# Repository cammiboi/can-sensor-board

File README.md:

# can-sensor-board

# Pupose
To attach any I2C sensor to a CAN bus.

# Requirements
* Powered by 5-16V DC
* Input and output connector (daisy chain boards)
* Set address on board
* I2C 4 pin connector to quickly connect different sensor boards
* Programming header
* ESD protection on connector pins

# Pinout
### CAN and Power Connectors (J1 and J2)

Both of these connectors are the same, you can plug input OR output in to either one.

Wire connector: Molex 1053081204

| Pin Number | Function |
|--|--|
|1| CAN H |
|2 | CAN L |
|3 | VIN |
|4 | GND|

### I2C Connectors (J3 and J4)

Works with Sensor boards that have Adafruit STEMMA QT or Sparkfun QWIIC connector.

| Pin Number | Function |
|--|--|
|1| GND |
|2 | 3V3 |
|3 | SDA |
|4 | SCL|

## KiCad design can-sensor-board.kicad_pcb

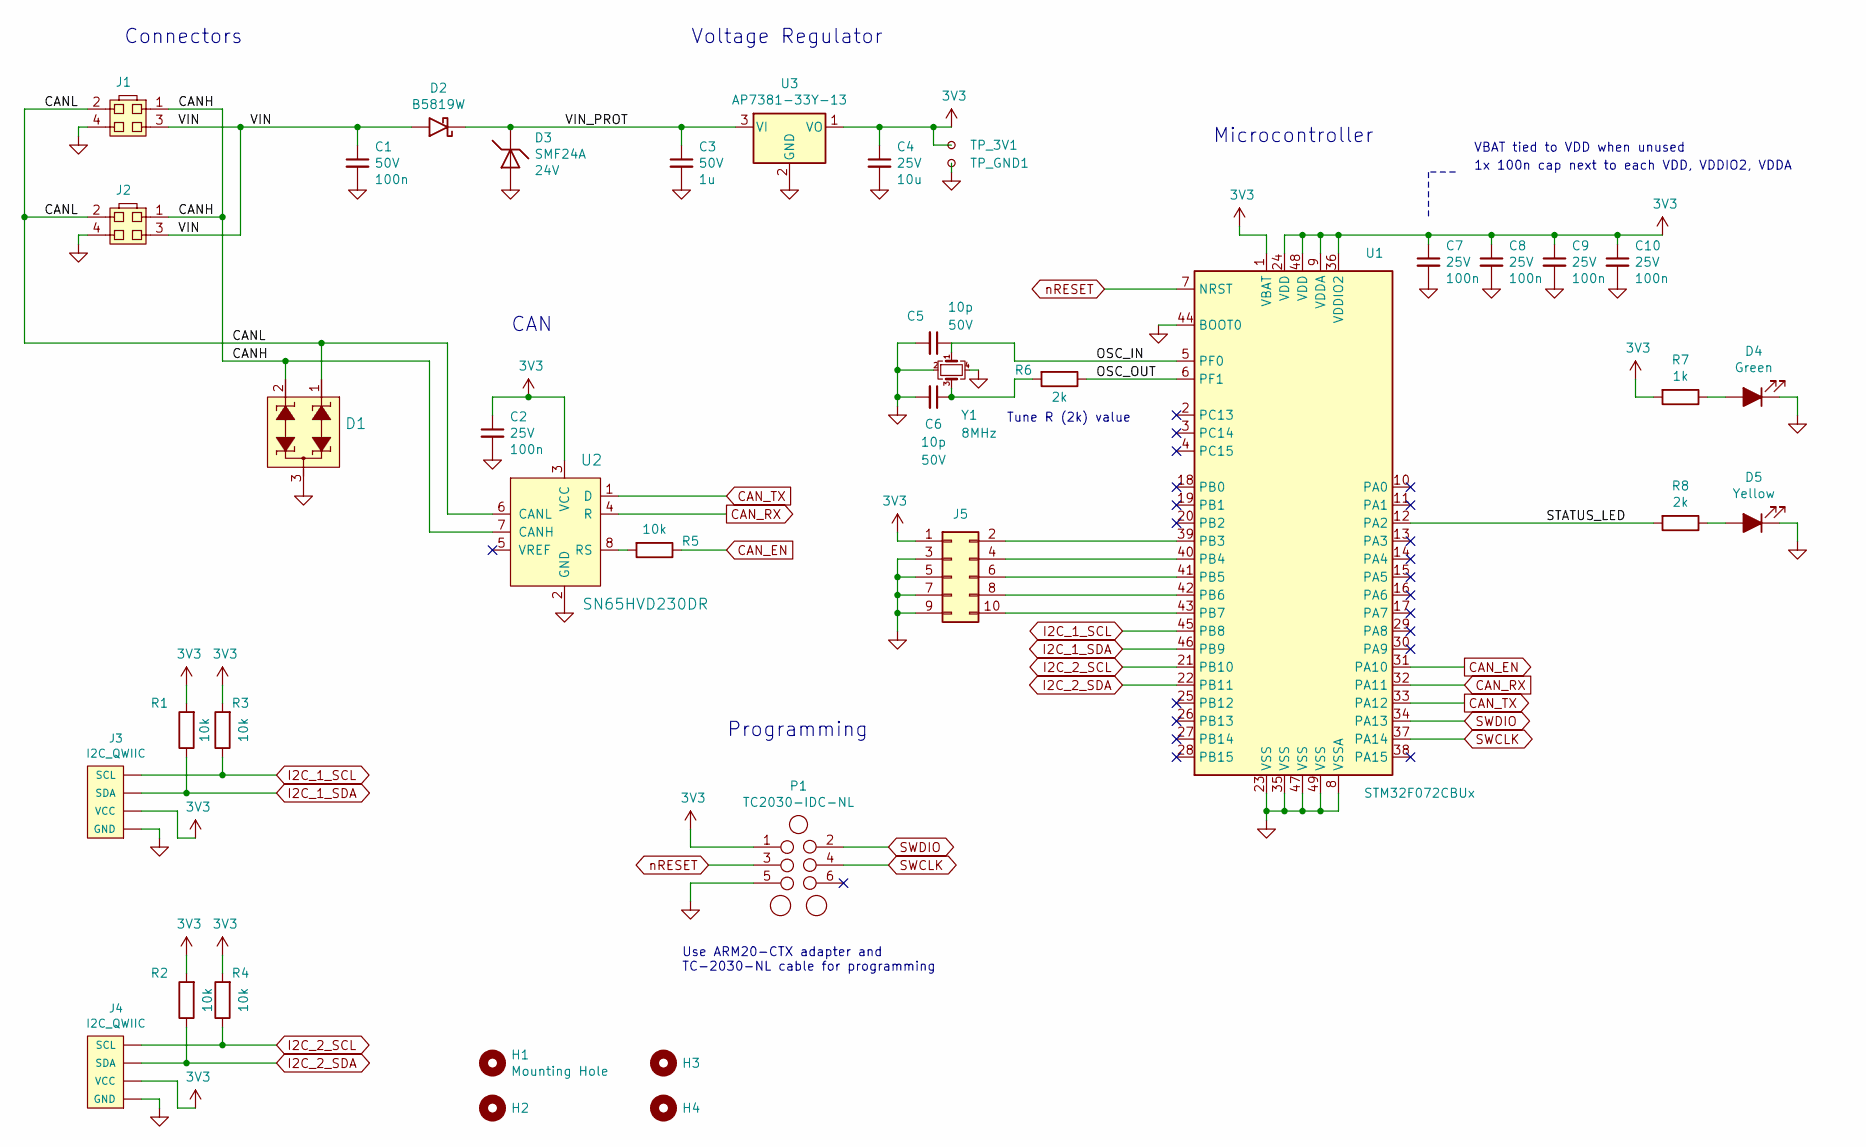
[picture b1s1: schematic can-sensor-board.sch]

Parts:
C1: C_0603_50V_X7R_100n; C_0603_1608Metric; Voltage 50V; Part Number CL10B104KB8NFNC; JLC C14663
C2, C7, C8, C9, C10: C_0402_25V_X7R_100n; C_0402_1005Metric; Voltage 25V; Manufacturer Part Number CL05B104KA5NNNC; JLC C100072
C3: C_0805_50V_X7R_1u; C_0805_2012Metric; Voltage 50V; Part Number CL21B105KBFNNNG; JLC C28323
C4: C_0805_25V_X5R_10u; C_0805_2012Metric; Voltage 25V; Part Number CL21A106KAYNNNG; JLC C15850
C5, C6: C_0402_50V_COG_10p; C_0402_1005Metric; Voltage 50V; JLC C32949
D1: PESD2CAN_215; SOT-23; MPN PESD2CAN,215; Digi-Key_PN 1727-3891-1-ND
D2: B5819W; D_SOD-123; Voltage 40V; JLC C8598
D3: SMF24A; D_SOD-123F; JLC C169430
D4: LED_0603_Green; LED_0603_1608Metric; JLC C72043
D5: LED_0603_Yellow; LED_0603_1608Metric; JLC C72038
H1, H2, H3, H4: Mounting Hole; MountingHole_3.2mm_M3; JLCPCB_IGNORE Yes
J1, J2: 105314-1104; Molex_Nano-Fit_105314-xx04_2x02_P2.50mm_Horizontal; JLCPCB_IGNORE Yes
J3, J4: I2C_QWIIC; JST_SH_SM04B-SRSS-TB_1x04-1MP_P1.00mm_Horizontal; Part Number SM04B-SRSS-TB(LF)(SN); JLC C395301
J5: Conn_02x05_Odd_Even; PinHeader_2x05_P2.54mm_Vertical; JLCPCB_IGNORE Yes
P1: TC2030-IDC-NL; Tag-Connect_TC2030-IDC-NL_2x03_P1.27mm_Vertical; JLCPCB_IGNORE Yes
R1, R2, R3, R4, R5: R_0603_10k_1; R_0603_1608Metric; JLC C25804
R6, R8: R_0402_2k_1; R_0402_1005Metric; JLC C4109
R7: R_0402_1k_1; R_0402_1005Metric; JLC C11702
TP_3V1: TestPoint_Small; TestPoint_Pad_D1.00mm; JLCPCB_IGNORE Yes
TP_GND1: TestPoint_Small; TestPoint_Pad_D1.00mm; JLCPCB_IGNORE Yes
U1: STM32F072CBUx; QFN-48-1EP_7x7mm_P0.5mm_EP5.6x5.6mm; JLC C92504
U2: SN65HVD230DR; SOIC-8_3.9x4.9mm_P1.27mm; MPN SN65HVD230DR; Digi-Key_PN 296-11654-1-ND
U3: AP7381-33Y-13; SOT-89-3; JLC C460411
Y1: TAXM8M4RDBCCT2T; Crystal_SMD_3225-4Pin_3.2x2.5mm; JLC C400090

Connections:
3V3: C2.1, C4.1, C7.1, C8.1, C9.1, C10.1, J3.2 (VCC), J4.2 (VCC), J5.1, P1.1, R1.2, R2.2, R3.2, R4.2, R7.2, TP_3V1.1, U1.1 (VBAT), U1.9 (VDDA), U1.24 (VDD), U1.36 (VDDIO2), U1.48 (VDD), U2.3 (VCC), U3.1 (VO)
/CANH: D1.2 (C2), J1.1, J2.1, U2.7 (CANH)
/CANL: D1.1 (C1), J1.2, J2.2, U2.6 (CANL)
/OSC_IN: C5.1, U1.5 (PF0), Y1.1
/OSC_OUT: R6.1, U1.6 (PF1)
/STATUS_LED: R8.2, U1.12 (PA2)
/VIN: C1.1, D2.2 (A), J1.3, J2.3
/VIN_PROT: C3.1, D2.1 (K), D3.1 (A1), U3.3 (VI)
CAN_EN: R5.1, U1.31 (PA10)
CAN_RX: U1.32 (PA11), U2.4 (R)
CAN_TX: U1.33 (PA12), U2.1 (D)
GND: C1.2, C2.2, C3.2, C4.2, C5.2, C6.2, C7.2, C8.2, C9.2, C10.2, D1.3 (C3), D3.2 (A2), D4.1 (K), D5.1 (K), J1.4 (3), J2.4 (3), J3.1 (GND), J4.1 (GND), J5.3, J5.5, J5.7, J5.9, P1.5, TP_GND1.1, U1.8 (VSSA), U1.23 (VSS), U1.35 (VSS), U1.44 (BOOT0), U1.47 (VSS), U1.49 (VSS), U2.2 (GND), U3.2 (GND), Y1.2, Y1.4
I2C_1_SCL: J3.4 (SCL), R3.1, U1.45 (PB8)
I2C_1_SDA: J3.3 (SDA), R1.1, U1.46 (PB9)
I2C_2_SCL: J4.4 (SCL), R4.1, U1.21 (PB10)
I2C_2_SDA: J4.3 (SDA), R2.1, U1.22 (PB11)
unnamed: C6.1, R6.2, Y1.3
unnamed: D4.2 (A), R7.1
unnamed: D5.2 (A), R8.1
unnamed: J5.2, U1.39 (PB3)
unnamed: J5.4, U1.40 (PB4)
unnamed: J5.6, U1.41 (PB5)
unnamed: J5.8, U1.42 (PB6)
unnamed: J5.10, U1.43 (PB7)
unnamed: R5.2, U2.8 (RS)
SWCLK: P1.4, U1.37 (PA14)
SWDIO: P1.2, U1.34 (PA13)
nRESET: P1.3, U1.7 (NRST)

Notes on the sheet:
Microcontroller
Connectors
Voltage Regulator
CAN
VBAT tied to VDD when unused
1x 100n cap next to each VDD, VDDIO2, VDDA
Use ARM20-CTX adapter and TC-2030-NL cable for programming
Programming
Tune R (2k) value

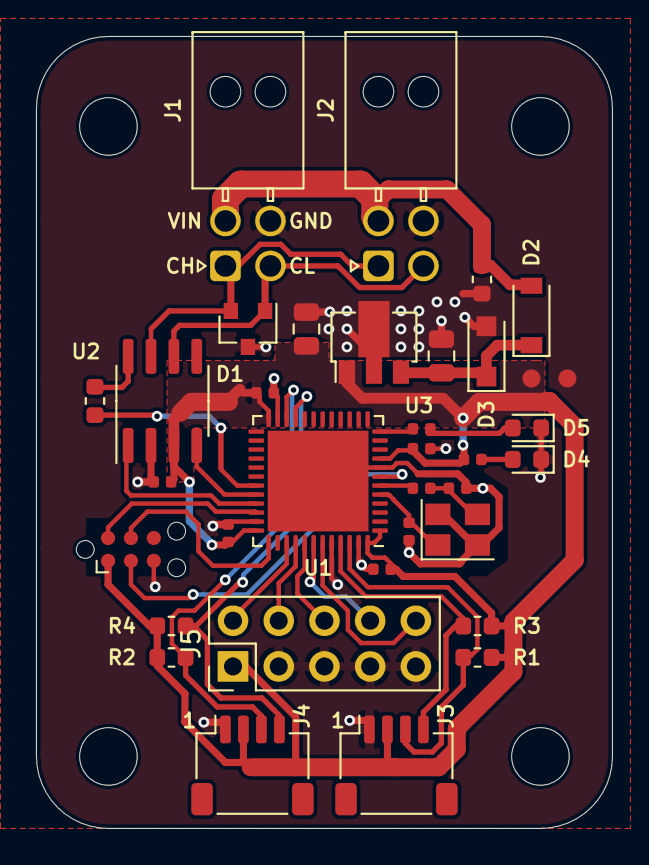
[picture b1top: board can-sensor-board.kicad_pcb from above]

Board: 2 copper layers, 32.0 x 44.0 mm, 39 parts (0 on the bottom side), 28 nets.

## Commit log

2021-04-23 schematic done
2021-04-24 final v1 board
2021-04-24 final v1 submitted for review
2021-04-24 Add image
